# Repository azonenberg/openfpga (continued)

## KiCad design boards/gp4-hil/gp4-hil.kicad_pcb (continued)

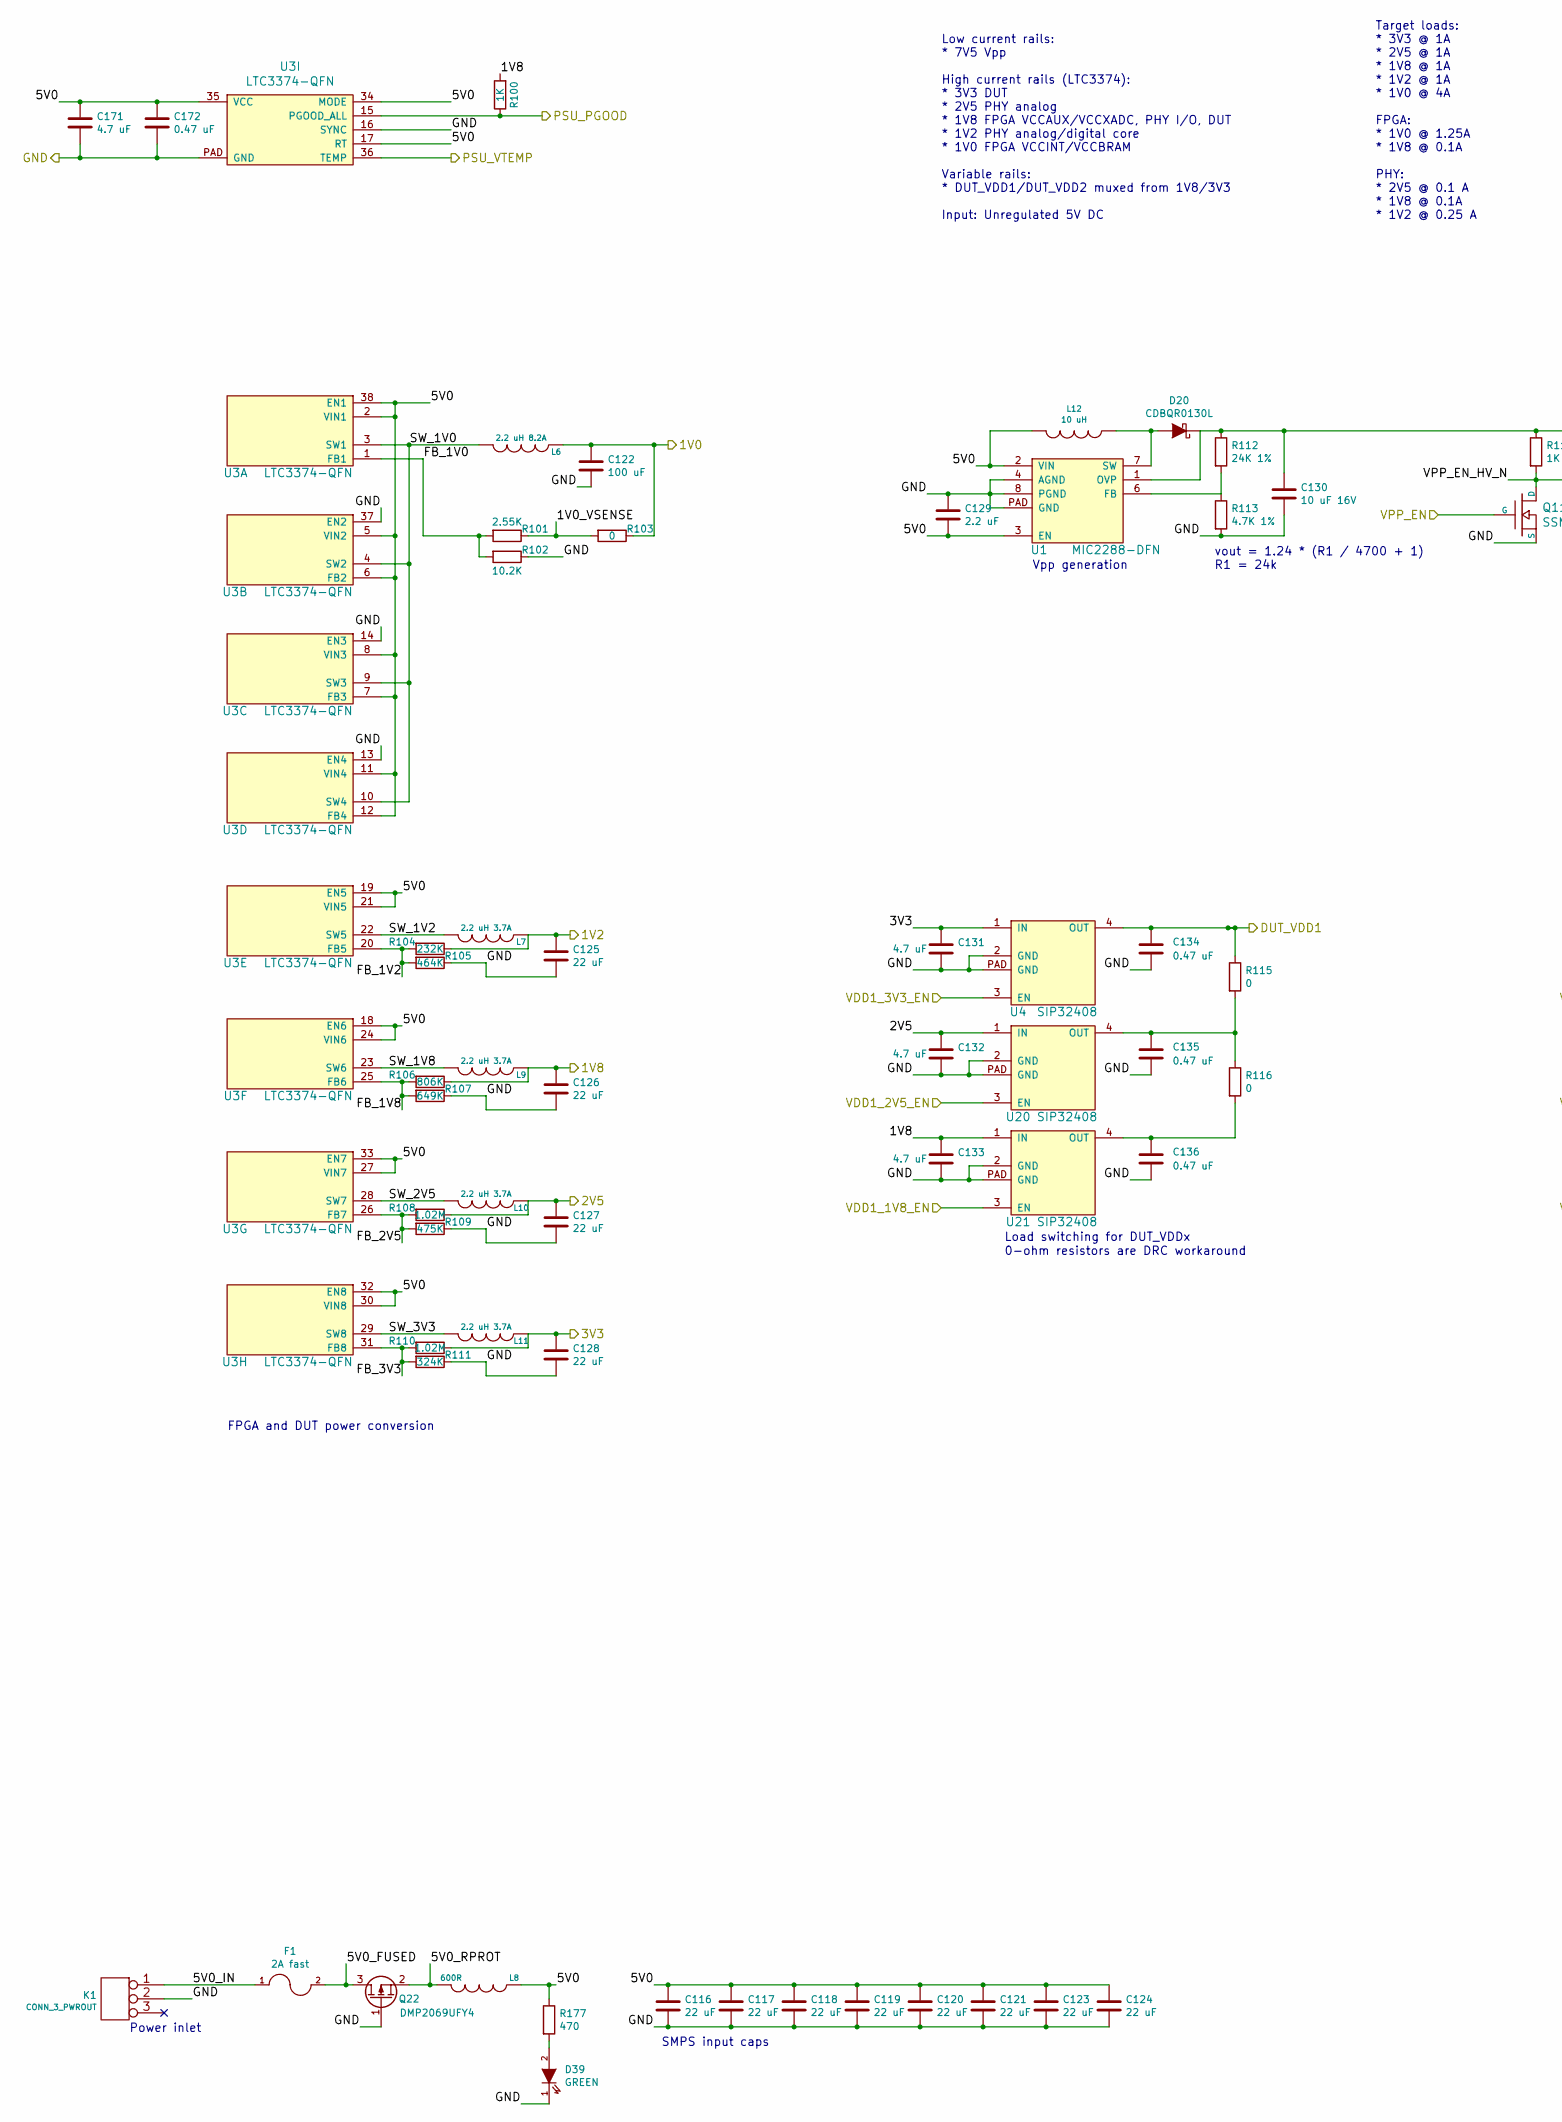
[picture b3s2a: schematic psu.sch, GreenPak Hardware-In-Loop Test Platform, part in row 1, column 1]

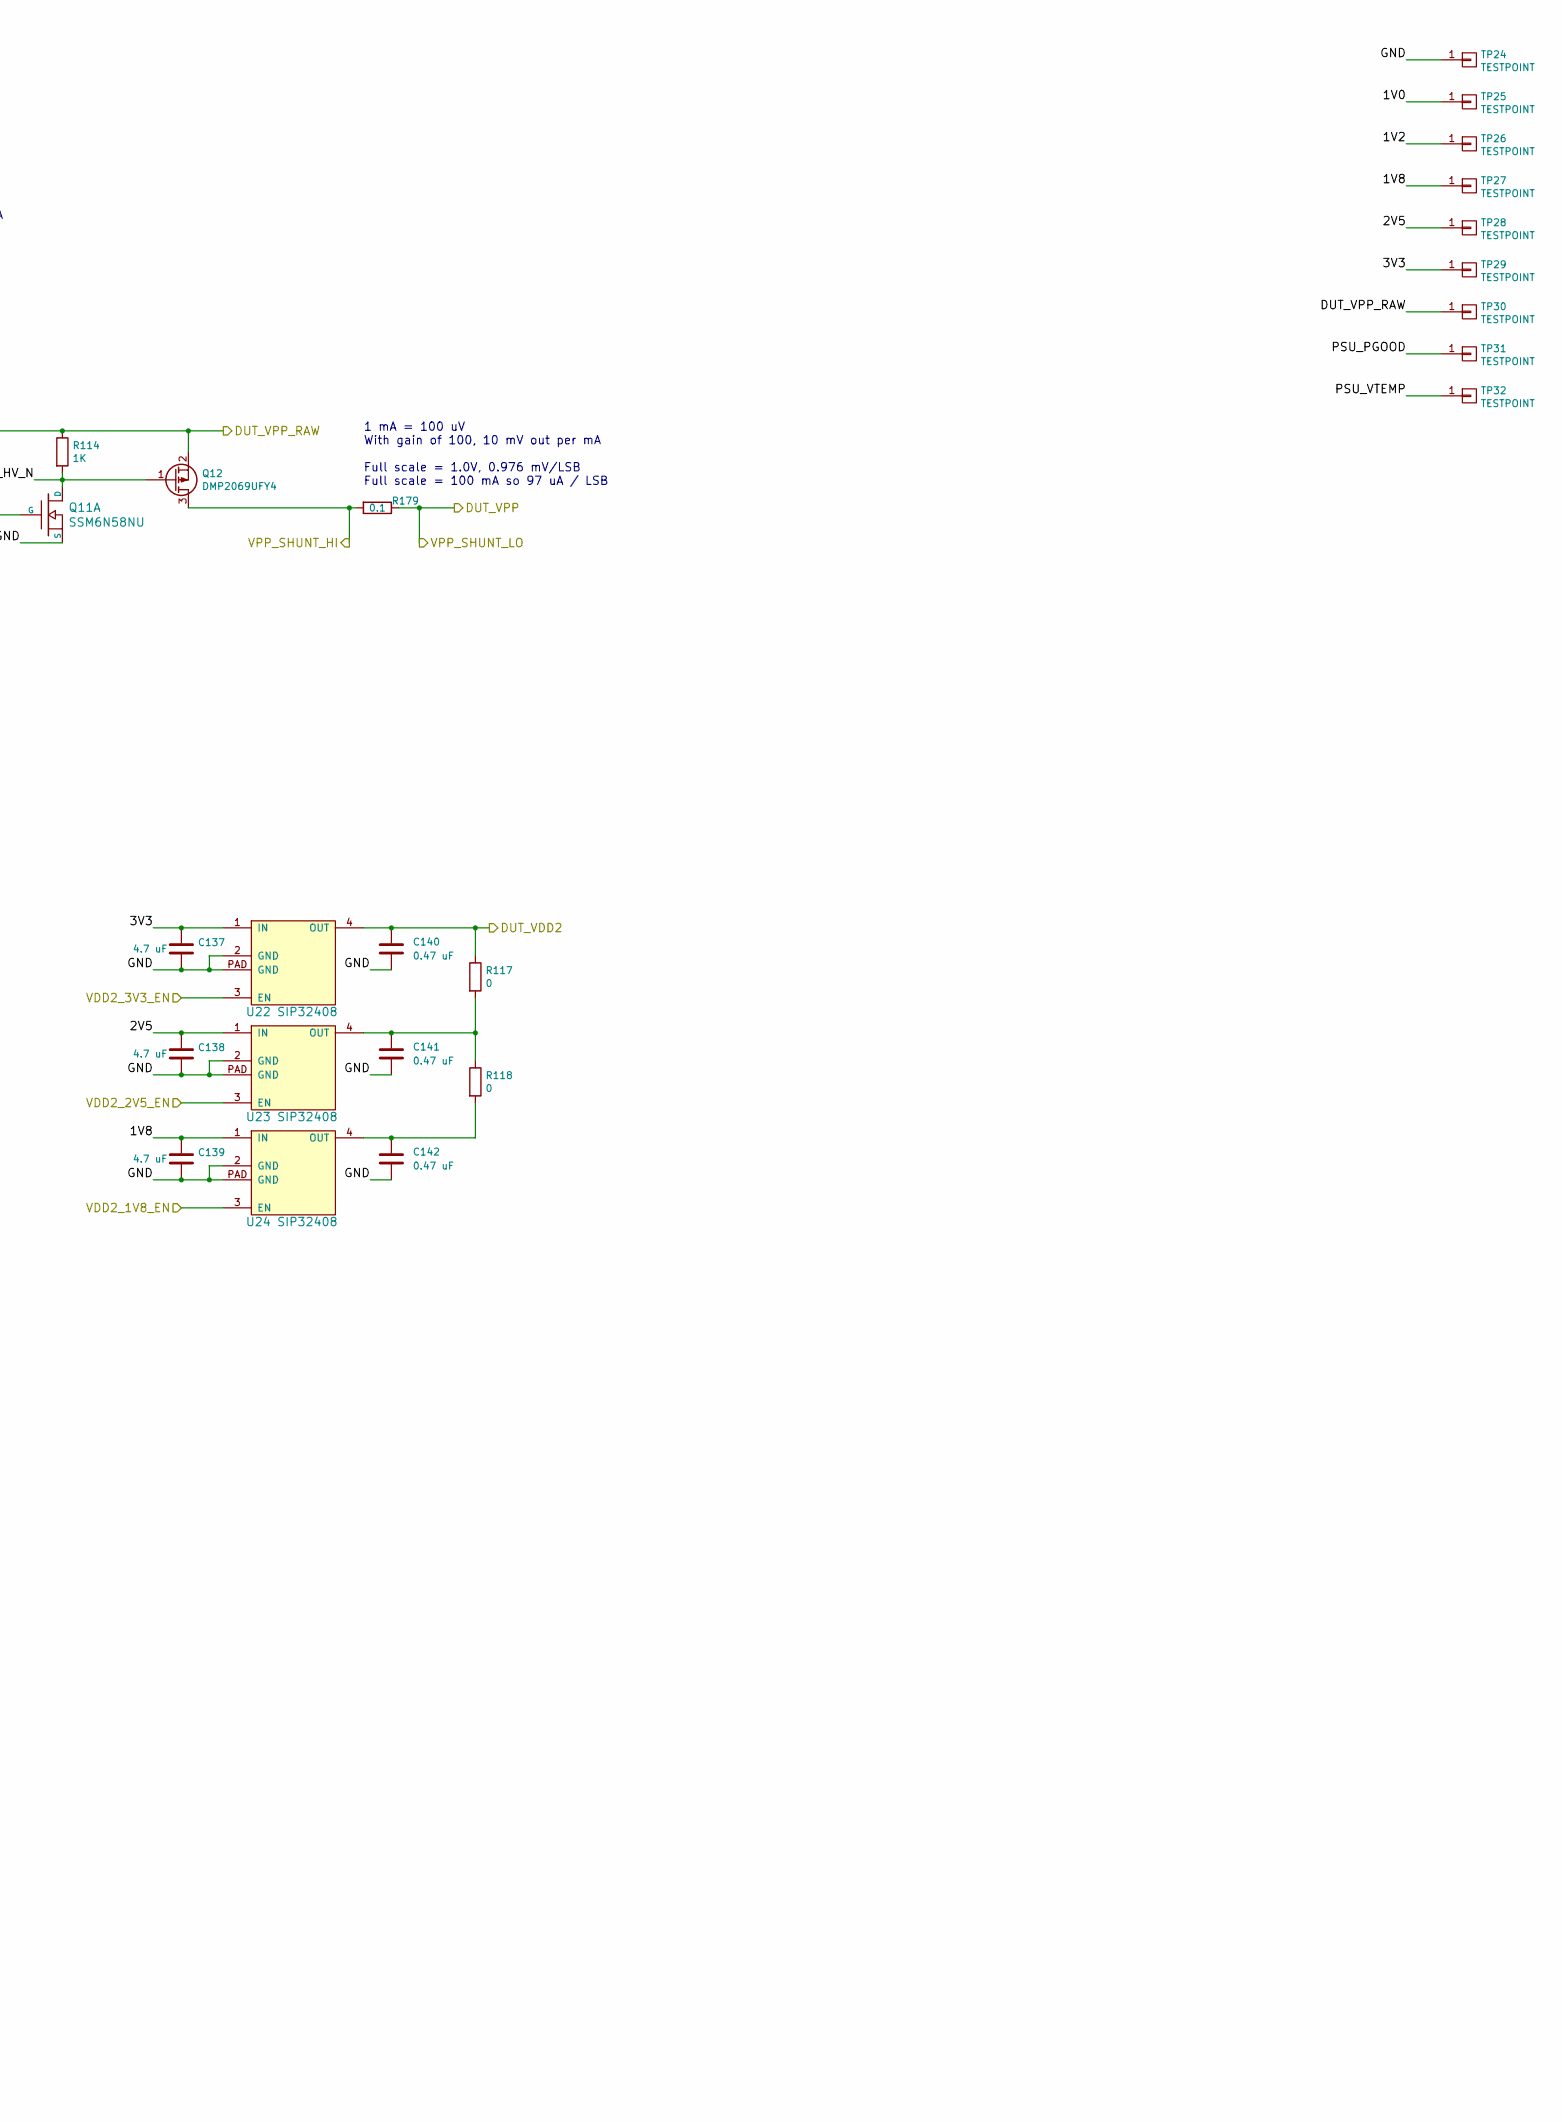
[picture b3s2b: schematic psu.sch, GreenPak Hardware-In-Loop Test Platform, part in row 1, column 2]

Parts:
C116, C117, C118, C119, C120, C121, C123, C124, C125, C126, C127, C128: 22 uF; EIA_1206_CAP_NOSILK
C122: 100 uF; EIA_1210_CAP_NOSILK
C129: 2.2 uF; EIA_1206_CAP_NOSILK
C130: 10 uF 16V; EIA_1206_CAP_NOSILK
C131, C132, C133, C137, C138, C139, C171: 4.7 uF; EIA_0603_CAP_NOSILK
C134, C135, C136, C140, C141, C142, C172: 0.47 uF; EIA_0402_CAP_NOSILK
D20: CDBQR0130L; EIA_0402_LED
D39: GREEN; EIA_0603_LED
F1: 2A fast; EIA_0402_RES_NOSILK
K1: CONN_3_PWROUT; CONN_CUI_PJ-058BH_HIPWR_BARREL_NOSLOT
L6: 2.2 uH 8.2A; INDUCTOR_TDK_SPM6530
L7, L9, L10, L11: 2.2 uH 3.7A; INDUCTOR_YUDEN_NR6028
L8: 600R; EIA_0603_INDUCTOR_NOSILK
L12: 10 uH; EIA_1210_CAP_NOSILK
Q11: SSM6N58NU; DFN_6_0.65MM_2x2MM_GDS
Q12, Q22: DMP2069UFY4; DFN_3_DIODES_X2DFN2015-3
R100, R114: 1K; EIA_0402_RES_NOSILK
R101: 2.55K; EIA_0402_RES_NOSILK
R102: 10.2K; EIA_0402_RES_NOSILK
R103, R115, R116, R117, R118: 0; EIA_0402_RES_NOSILK
R104: 232K; EIA_0402_RES_NOSILK
R105: 464K; EIA_0402_RES_NOSILK
R106: 806K; EIA_0402_RES_NOSILK
R107: 649K; EIA_0402_RES_NOSILK
R108, R110: 1.02M; EIA_0402_RES_NOSILK
R109: 475K; EIA_0402_RES_NOSILK
R111: 324K; EIA_0402_RES_NOSILK
R112: 24K 1%; EIA_0402_RES_NOSILK
R113: 4.7K 1%; EIA_0402_RES_NOSILK
R177: 470; EIA_0402_RES_NOSILK
R179: 0.1; EIA_0402_RES_NOSILK
TP24, TP25, TP26, TP27, TP28, TP29, TP30, TP31, TP32: TESTPOINT; TESTPOINT_SMT_KEYSTONE_5016
U1: MIC2288-DFN; DFN_8_0.5MM_2x2MM
U3: LTC3374-QFN; QFN_38_0.5MM_5x7MM
U4, U20, U21, U22, U23, U24: SIP32408; DFN_4_0.5MM_1.6x1.2MM

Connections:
/Analog IO/1V8: C126.1, C133.1, C139.1, L9.1, R100.2, R106.1, TP27.1, U21.1 (IN), U24.1 (IN); also elsewhere on the board
/Analog IO/2V5: C127.1, C132.1, C138.1, L10.1, R108.1, TP28.1, U20.1 (IN), U23.1 (IN); also elsewhere on the board
/Analog IO/3V3: C128.1, C131.1, C137.1, L11.1, R110.1, TP29.1, U4.1 (IN), U22.1 (IN); also elsewhere on the board
/Analog IO/DUT_GPIO2: R179.1; also elsewhere on the board
/Analog IO/DUT_VDD1: C134.1, R115.1, U4.4 (OUT); also elsewhere on the board
/Analog IO/DUT_VDD2: C140.1, R117.1, U22.4 (OUT); also elsewhere on the board
/Analog IO/DUT_VPP: C130.1, D20.1 (K), Q12.2 (S), R112.1, R114.1, TP30.1, U1.1 (OVP); also elsewhere on the board
/Analog IO/GND: C116.2, C117.2, C118.2, C119.2, C120.2, C121.2, C122.2, C123.2, C124.2, C125.2, C126.2, C127.2, C128.2, C129.1, C130.2, C131.2, C132.2, C133.2, C134.2, C135.2, C136.2, C137.2, C138.2, C139.2, C140.2, C141.2, C142.2, C171.2, C172.2, D39.1 (K), K1.2 (PM), Q11.S1 (S), Q22.1 (G), R102.1, R105.1, R107.1, R109.1, R111.1, R113.2, TP24.1, U1.4 (AGND), U1.8 (PGND), U1.PAD (GND), U3.13 (EN4), U3.14 (EN3), U3.16 (SYNC), U3.37 (EN2), U3.PAD (GND), U4.2 (GND), U4.PAD (GND), U20.2 (GND), U20.PAD (GND), U21.2 (GND), U21.PAD (GND), U22.2 (GND), U22.PAD (GND), U23.2 (GND), U23.PAD (GND), U24.2 (GND), U24.PAD (GND); also elsewhere on the board
/Analog IO/PSU_VTEMP: TP32.1, U3.36 (TEMP); also elsewhere on the board
/Analog IO/VPP_SHUNT_HI: Q12.3 (D), R179.2; also elsewhere on the board
/Ethernet + JTAG/1V2: C125.1, L7.1, R104.1, TP26.1; also elsewhere on the board
/Ethernet + JTAG/VDD1_1V8_EN: U21.3 (EN); also elsewhere on the board
/Ethernet + JTAG/VDD1_2V5_EN: U20.3 (EN); also elsewhere on the board
/Ethernet + JTAG/VDD1_3V3_EN: U4.3 (EN); also elsewhere on the board
/Ethernet + JTAG/VDD2_1V8_EN: U24.3 (EN); also elsewhere on the board
/Ethernet + JTAG/VDD2_2V5_EN: U23.3 (EN); also elsewhere on the board
/Ethernet + JTAG/VDD2_3V3_EN: U22.3 (EN); also elsewhere on the board
/Ethernet + JTAG/VPP_EN: Q11.G1 (G); also elsewhere on the board
/FPGA support/1V0: C122.1, L6.1, R103.1, TP25.1; also elsewhere on the board
/FPGA support/PSU_PGOOD: R100.1, TP31.1, U3.15 (PGOOD_ALL); also elsewhere on the board
/Power supply/1V0_VSENSE: R101.1, R103.2
/Power supply/5V0: C116.1, C117.1, C118.1, C119.1, C120.1, C121.1, C123.1, C124.1, C129.2, C171.1, C172.1, L8.1, L12.2, R177.1, U1.2 (VIN), U1.3 (EN), U3.2 (VIN1), U3.5 (VIN2), U3.6 (FB2), U3.7 (FB3), U3.8 (VIN3), U3.11 (VIN4), U3.12 (FB4), U3.17 (RT), U3.18 (EN6), U3.19 (EN5), U3.21 (VIN5), U3.24 (VIN6), U3.27 (VIN7), U3.30 (VIN8), U3.32 (EN8), U3.33 (EN7), U3.34 (MODE), U3.35 (VCC), U3.38 (EN1)
/Power supply/5V0_FUSED: F1.2, Q22.3 (D)
/Power supply/5V0_IN: F1.1, K1.1
/Power supply/5V0_RPROT: L8.2, Q22.2 (S)
/Power supply/FB_1V0: R101.2, R102.2, U3.1 (FB1)
/Power supply/FB_1V2: R104.2, R105.2, U3.20 (FB5)
/Power supply/FB_1V8: R106.2, R107.2, U3.25 (FB6)
/Power supply/FB_2V5: R108.2, R109.2, U3.26 (FB7)
/Power supply/FB_3V3: R110.2, R111.2, U3.31 (FB8)
/Power supply/SW_1V0: L6.2, U3.3 (SW1), U3.4 (SW2), U3.9 (SW3), U3.10 (SW4)
/Power supply/SW_1V2: L7.2, U3.22 (SW5)
/Power supply/SW_1V8: L9.2, U3.23 (SW6)
/Power supply/SW_2V5: L10.2, U3.28 (SW7)
/Power supply/SW_3V3: L11.2, U3.29 (SW8)
/Power supply/VPP_EN_HV_N: Q11.D1 (D), Q12.1 (G), R114.2
unnamed: C135.1, R115.2, R116.1, U20.4 (OUT)
unnamed: C136.1, R116.2, U21.4 (OUT)
unnamed: C141.1, R117.2, R118.1, U23.4 (OUT)
unnamed: C142.1, R118.2, U24.4 (OUT)
unnamed: D20.2 (A), L12.1, U1.7 (SW)
unnamed: D39.2 (A), R177.2
unnamed: R112.2, R113.1, U1.6 (FB)

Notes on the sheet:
Low current rails: * 7V5 Vpp High current rails (LTC3374): * 3V3 DUT * 2V5 PHY analog * 1V8 FPGA VCCAUX/VCCXADC, PHY I/O, DUT * 1V2 PHY analog/digital core * 1V0 FPGA VCCINT/VCCBRAM Variable rails: * DUT_VDD1/DUT_VDD2 muxed from 1V8/3V3 Input: Unregulated 5V DC
Power inlet
Target loads: * 3V3 @ 1A * 2V5 @ 1A * 1V8 @ 1A * 1V2 @ 1A * 1V0 @ 4A FPGA: * 1V0 @ 1.25A * 1V8 @ 0.1A PHY: * 2V5 @ 0.1 A * 1V8 @ 0.1A * 1V2 @ 0.25 A
SMPS input caps
vout = 1.24 * (R1 / 4700 + 1) R1 = 24k
Load switching for DUT_VDDx
Vpp generation
FPGA and DUT power conversion
0-ohm resistors are DRC workaround
1 mA = 100 uV With gain of 100, 10 mV out per mA Full scale = 1.0V, 0.976 mV/LSB Full scale = 100 mA so 97 uA / LSB

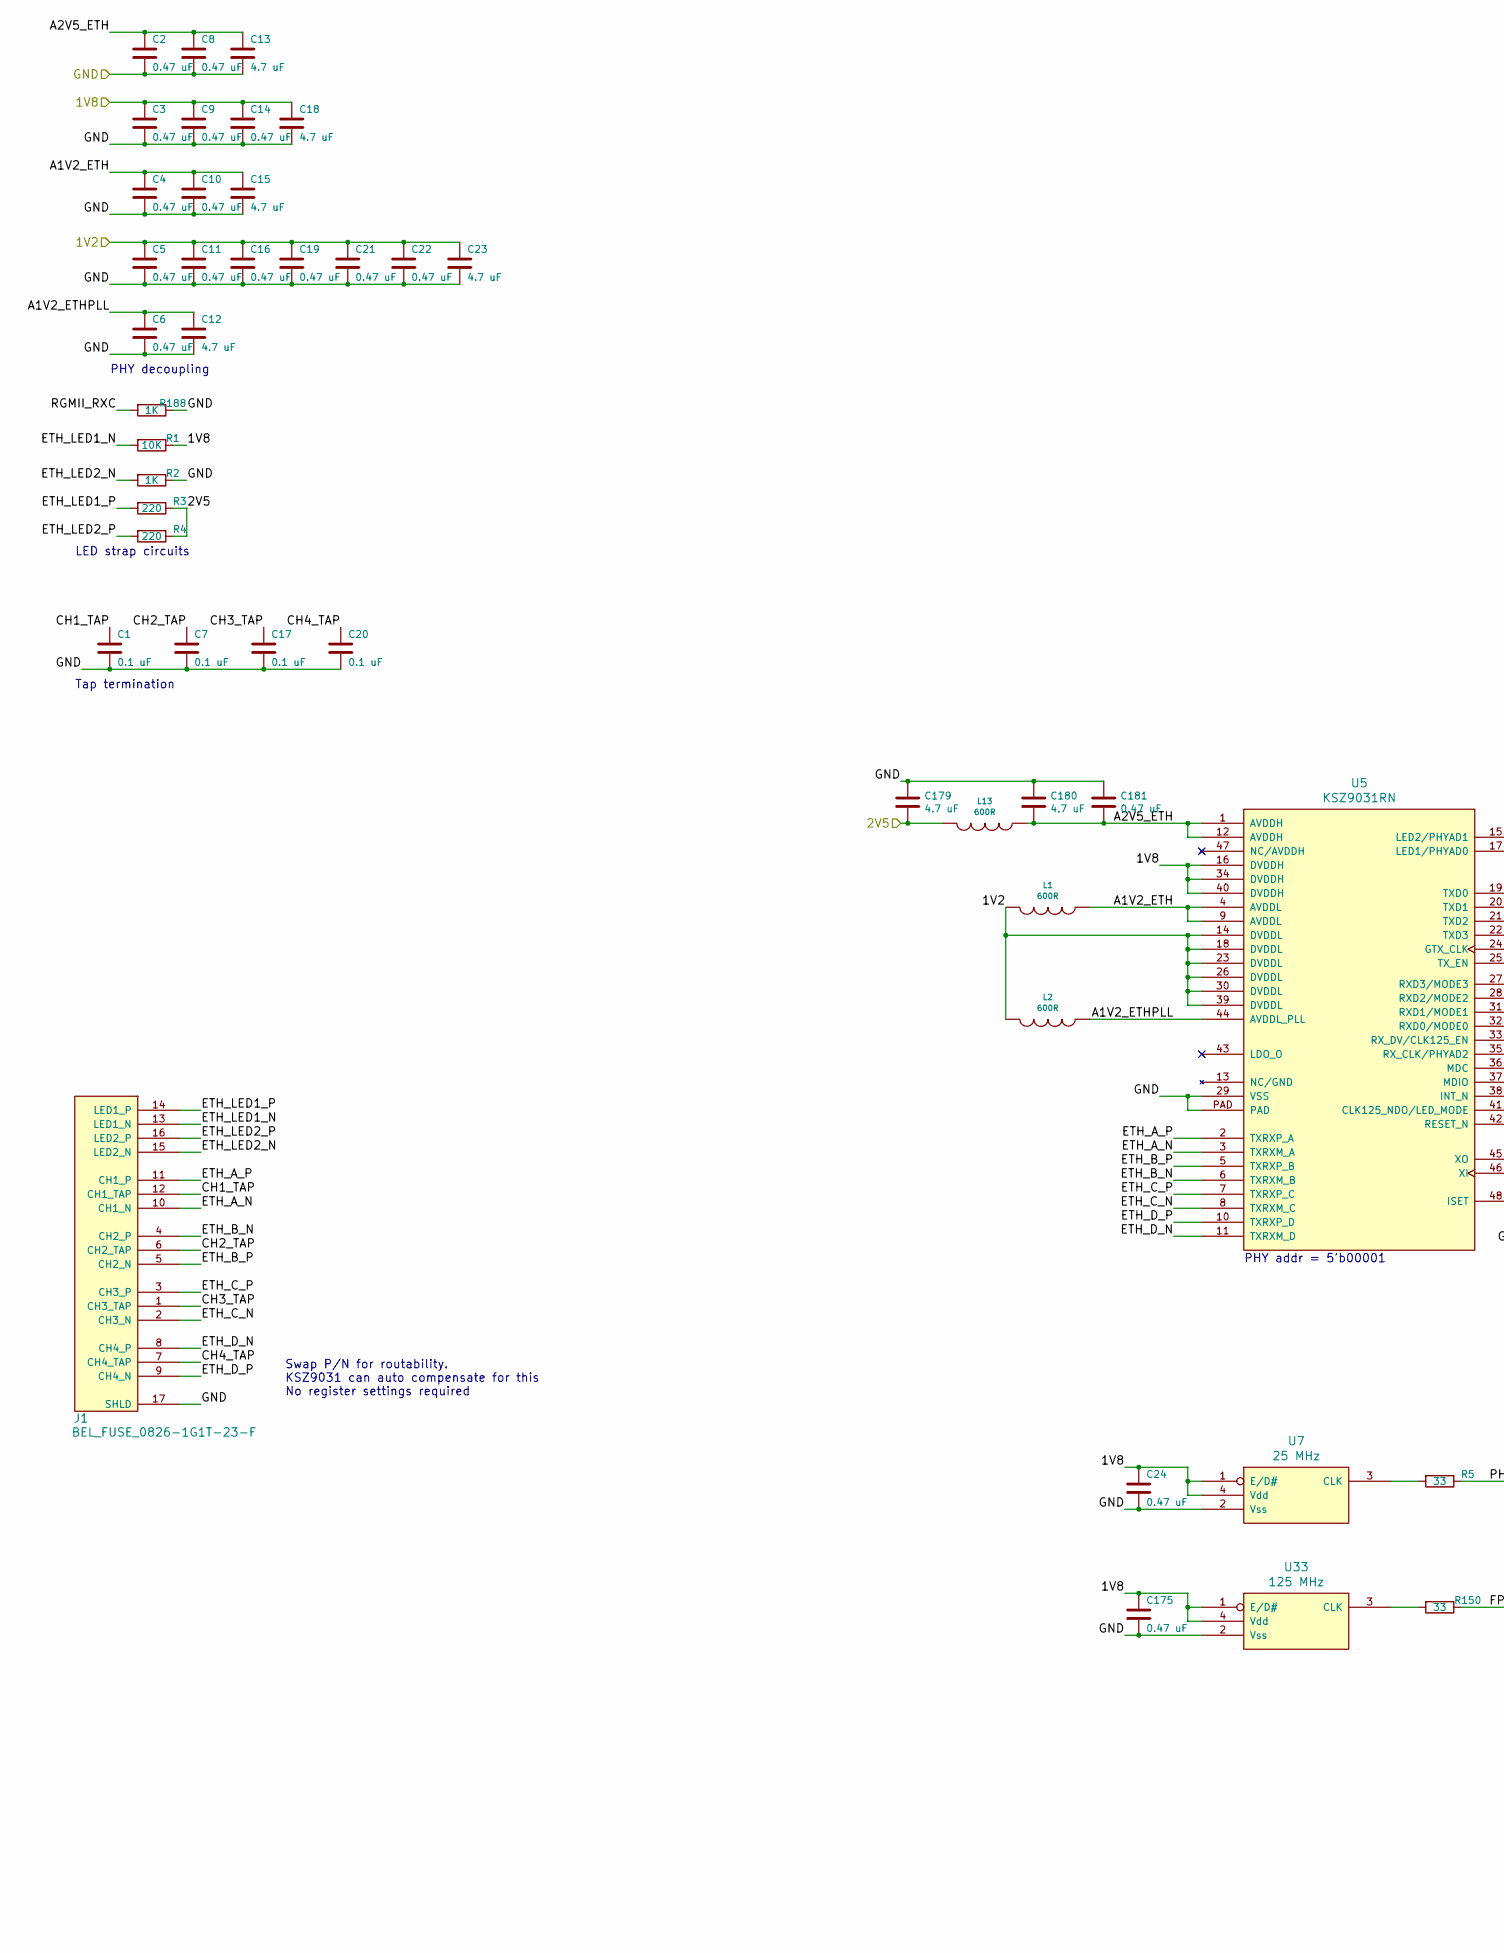
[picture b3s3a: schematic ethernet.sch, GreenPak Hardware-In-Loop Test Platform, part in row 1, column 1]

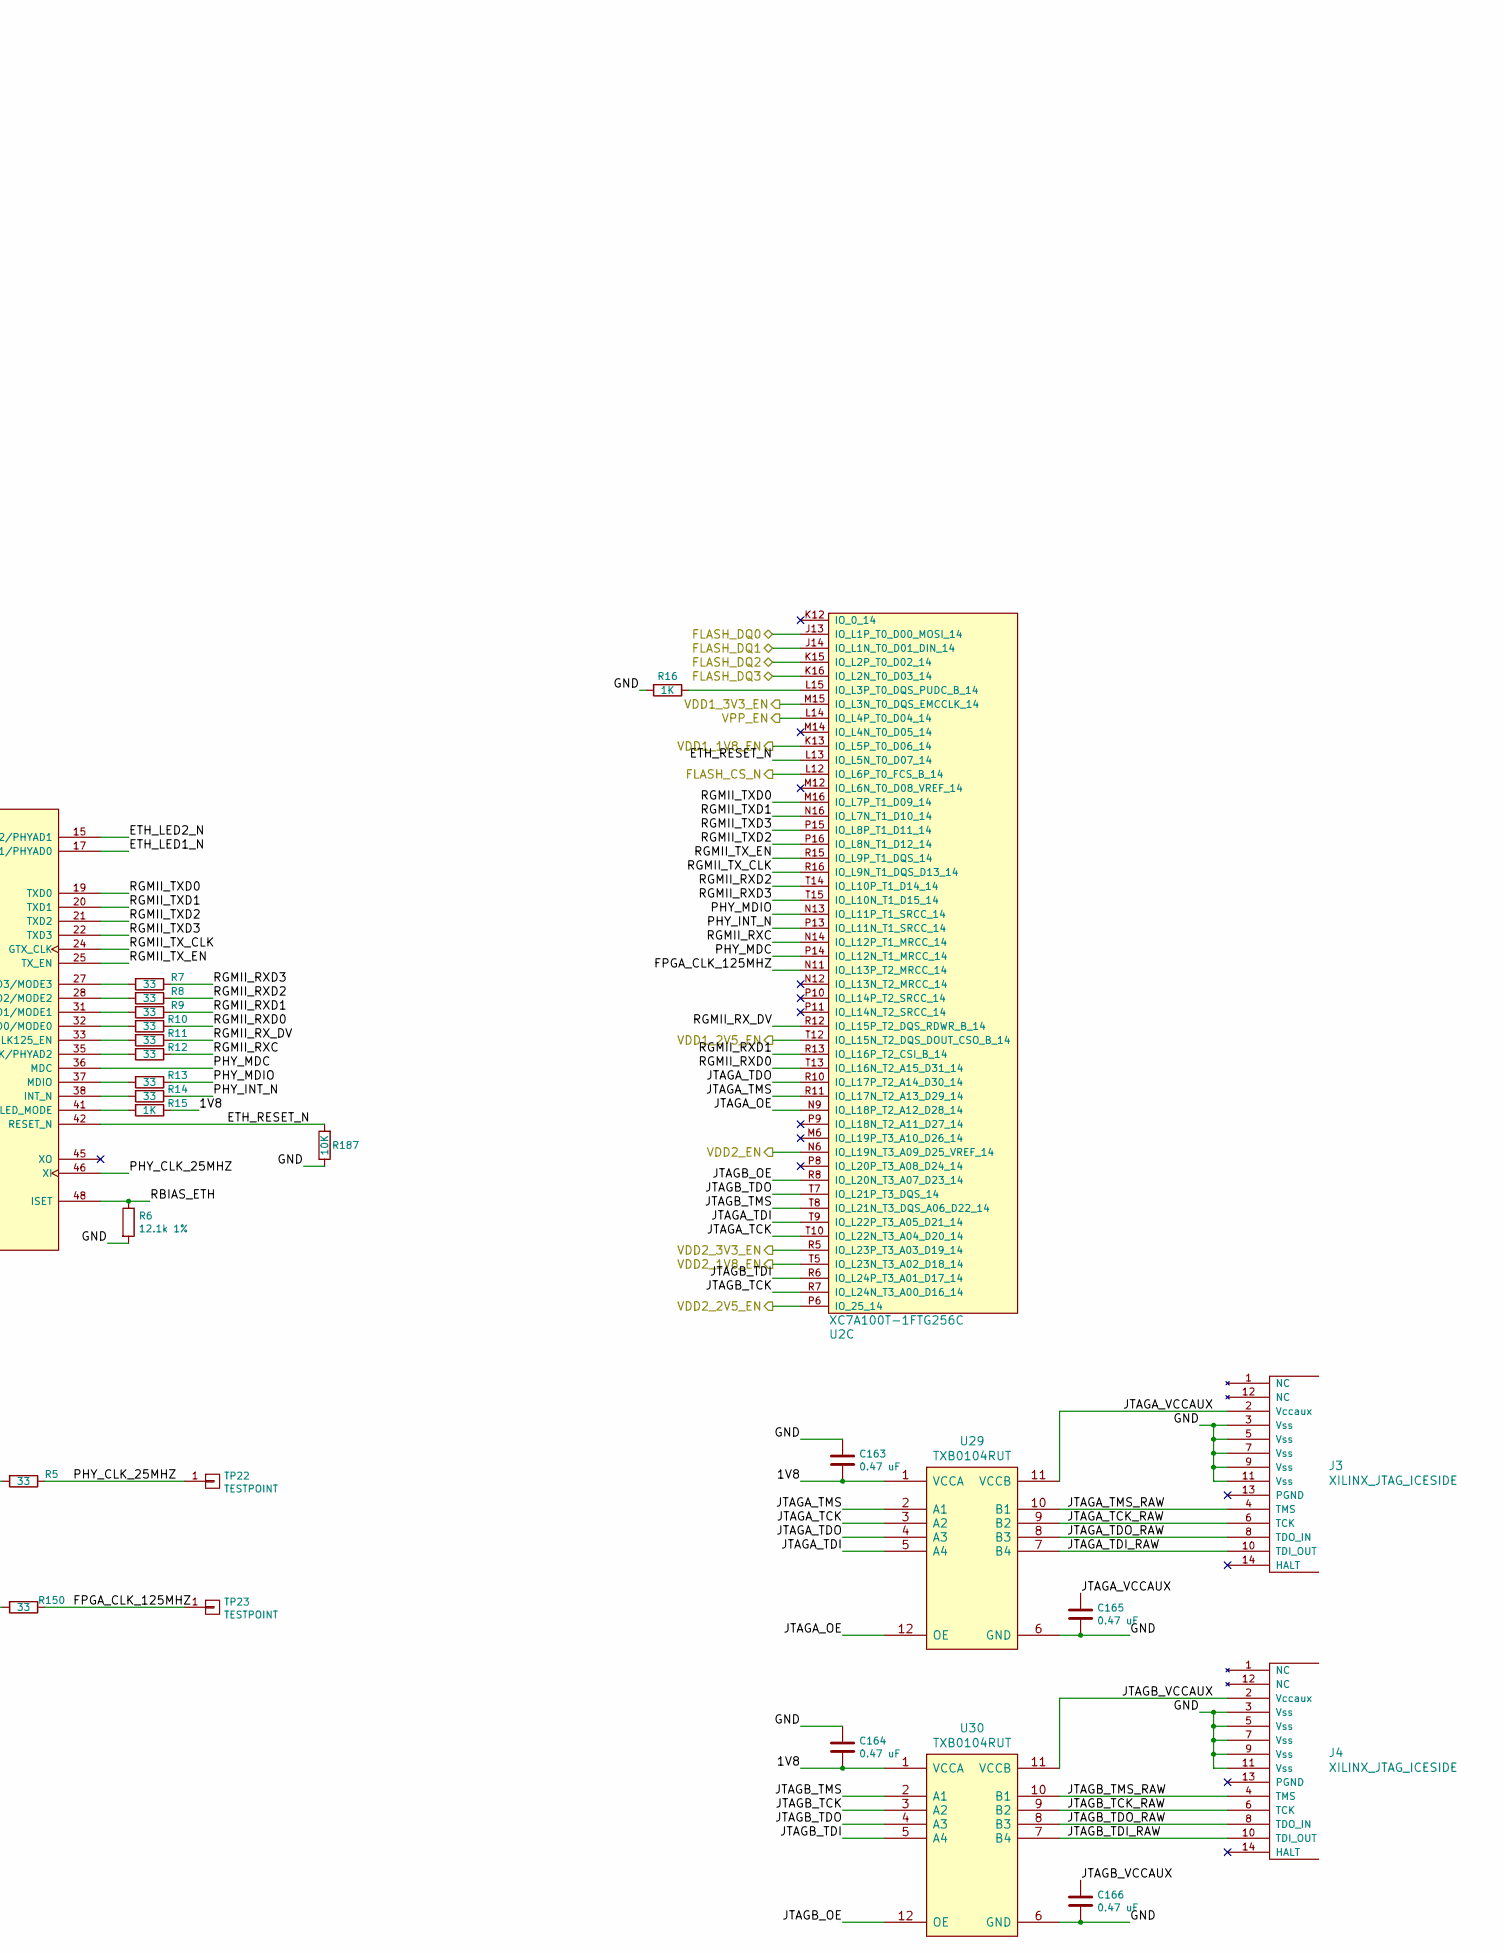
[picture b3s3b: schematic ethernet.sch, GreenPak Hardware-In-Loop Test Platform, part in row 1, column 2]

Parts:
C1, C7, C17, C20: 0.1 uF; EIA_0402_CAP_NOSILK
C2, C3, C4, C5, C6, C8, C9, C10, C11, C14, C16, C19, C21, C22, C24, C163, C164, C165, C166, C175, C181: 0.47 uF; EIA_0402_CAP_NOSILK
C12, C13, C15, C18, C23, C179, C180: 4.7 uF; EIA_0603_CAP_NOSILK
J1: BEL_FUSE_0826-1G1T-23-F; CONN_BELFUSE_0826_1G1T_23_F
J3, J4: XILINX_JTAG_ICESIDE; XILINX_JTAG_PTH_MOLEX_0878311420
L1, L2, L13: 600R; EIA_0603_INDUCTOR_NOSILK
R1, R187: 10K; EIA_0402_RES_NOSILK
R2, R15, R16, R188: 1K; EIA_0402_RES_NOSILK
R3, R4: 220; EIA_0402_RES_NOSILK
R5, R7, R8, R9, R10, R11, R12, R13, R14, R150: 33; EIA_0402_RES_NOSILK
R6: 12.1k 1%; EIA_0402_RES_NOSILK
TP22, TP23: TESTPOINT; TESTPOINT_SMT_0.5MM
U2: XC7A100T-1FTG256C; BGA_256_17x17_FULLARRAY_1MM
U5: KSZ9031RN; QFN_48_0.5MM_7x7MM
U7: 25 MHz; OSCILLATOR_2.0x1.6
U29, U30: TXB0104RUT; QFN_12_0.4MM_2x2MM
U33: 125 MHz; OSCILLATOR_2.0x1.6

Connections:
/Analog IO/1V8: C3.1, C9.1, C14.1, C18.1, C24.1, C163.2, C164.2, C175.1, R1.1, R15.1, U5.16 (DVDDH), U5.34 (DVDDH), U5.40 (DVDDH), U7.1 (E/D#), U7.4 (Vdd), U29.1 (VCCA), U30.1 (VCCA), U33.1 (E/D#), U33.4 (Vdd); also elsewhere on the board
/Analog IO/2V5: C179.2, L13.2, R3.1, R4.1; also elsewhere on the board
/Analog IO/GND: C1.2, C2.2, C3.2, C4.2, C5.2, C6.2, C7.2, C8.2, C9.2, C10.2, C11.2, C12.2, C13.2, C14.2, C15.2, C16.2, C17.2, C18.2, C19.2, C20.2, C21.2, C22.2, C23.2, C24.2, C163.1, C164.1, C165.2, C166.2, C175.2, C179.1, C180.1, C181.1, J1.17 (SHLD), J3.3 (Vss), J3.5 (Vss), J3.7 (Vss), J3.9 (Vss), J3.11 (Vss), J4.3 (Vss), J4.5 (Vss), J4.7 (Vss), J4.9 (Vss), J4.11 (Vss), R2.1, R6.2, R16.2, R187.1, R188.1, U5.29 (VSS), U5.PAD, U7.2 (Vss), U29.6 (GND), U30.6 (GND), U33.2 (Vss); also elsewhere on the board
/DUT/DUT_VDD2_EN: U2.N6 (IO_L19N_T3_A09_D25_VREF_14); also elsewhere on the board
/Ethernet + JTAG/1V2: C5.1, C11.1, C16.1, C19.1, C21.1, C22.1, C23.1, L1.2, L2.2, U5.14 (DVDDL), U5.18 (DVDDL), U5.23 (DVDDL), U5.26 (DVDDL), U5.30 (DVDDL), U5.39 (DVDDL); also elsewhere on the board
/Ethernet + JTAG/A1V2_ETH: C4.1, C10.1, C15.1, L1.1, U5.4 (AVDDL), U5.9 (AVDDL)
/Ethernet + JTAG/A1V2_ETHPLL: C6.1, C12.1, L2.1, U5.44 (AVDDL_PLL)
/Ethernet + JTAG/A2V5_ETH: C2.1, C8.1, C13.1, C180.2, C181.2, L13.1, U5.1 (AVDDH), U5.12 (AVDDH)
/Ethernet + JTAG/CH1_TAP: C1.1, J1.12 (CH1_TAP)
/Ethernet + JTAG/CH2_TAP: C7.1, J1.6 (CH2_TAP)
/Ethernet + JTAG/CH3_TAP: C17.1, J1.1 (CH3_TAP)
/Ethernet + JTAG/CH4_TAP: C20.1, J1.7 (CH4_TAP)
/Ethernet + JTAG/ETH_A_N: J1.10 (CH1_N), U5.3 (TXRXM_A)
/Ethernet + JTAG/ETH_A_P: J1.11 (CH1_P), U5.2 (TXRXP_A)
/Ethernet + JTAG/ETH_B_N: J1.4 (CH2_P), U5.6 (TXRXM_B)
/Ethernet + JTAG/ETH_B_P: J1.5 (CH2_N), U5.5 (TXRXP_B)
/Ethernet + JTAG/ETH_C_N: J1.2 (CH3_N), U5.8 (TXRXM_C)
/Ethernet + JTAG/ETH_C_P: J1.3 (CH3_P), U5.7 (TXRXP_C)
/Ethernet + JTAG/ETH_D_N: J1.8 (CH4_P), U5.11 (TXRXM_D)
/Ethernet + JTAG/ETH_D_P: J1.9 (CH4_N), U5.10 (TXRXP_D)
/Ethernet + JTAG/ETH_LED1_N: J1.13 (LED1_N), R1.2, U5.17 (LED1/PHYAD0)
/Ethernet + JTAG/ETH_LED1_P: J1.14 (LED1_P), R3.2
/Ethernet + JTAG/ETH_LED2_N: J1.15 (LED2_N), R2.2, U5.15 (LED2/PHYAD1)
/Ethernet + JTAG/ETH_LED2_P: J1.16 (LED2_P), R4.2
/Ethernet + JTAG/ETH_RESET_N: R187.2, U2.L13 (IO_L5N_T0_D07_14), U5.42 (RESET_N)
/Ethernet + JTAG/FLASH_CS_N: U2.L12 (IO_L6P_T0_FCS_B_14); also elsewhere on the board
/Ethernet + JTAG/FLASH_DQ0: U2.J13 (IO_L1P_T0_D00_MOSI_14); also elsewhere on the board
/Ethernet + JTAG/FLASH_DQ1: U2.J14 (IO_L1N_T0_D01_DIN_14); also elsewhere on the board
/Ethernet + JTAG/FLASH_DQ2: U2.K15 (IO_L2P_T0_D02_14); also elsewhere on the board
/Ethernet + JTAG/FLASH_DQ3: U2.K16 (IO_L2N_T0_D03_14); also elsewhere on the board
/Ethernet + JTAG/FPGA_CLK_125MHZ: R150.1, TP23.1, U2.N11 (IO_L13P_T2_MRCC_14)
/Ethernet + JTAG/JTAGA_OE: U2.N9 (IO_L18P_T2_A12_D28_14), U29.12 (OE)
/Ethernet + JTAG/JTAGA_TCK: U2.T10 (IO_L22N_T3_A04_D20_14), U29.3 (A2)
/Ethernet + JTAG/JTAGA_TCK_RAW: J3.6 (TCK), U29.9 (B2)
/Ethernet + JTAG/JTAGA_TDI: U2.T9 (IO_L22P_T3_A05_D21_14), U29.5 (A4)
/Ethernet + JTAG/JTAGA_TDI_RAW: J3.10 (TDI_OUT), U29.7 (B4)
/Ethernet + JTAG/JTAGA_TDO: U2.R10 (IO_L17P_T2_A14_D30_14), U29.4 (A3)
/Ethernet + JTAG/JTAGA_TDO_RAW: J3.8 (TDO_IN), U29.8 (B3)
/Ethernet + JTAG/JTAGA_TMS: U2.R11 (IO_L17N_T2_A13_D29_14), U29.2 (A1)
/Ethernet + JTAG/JTAGA_TMS_RAW: J3.4 (TMS), U29.10 (B1)
/Ethernet + JTAG/JTAGA_VCCAUX: C165.1, J3.2 (Vccaux), U29.11 (VCCB)
/Ethernet + JTAG/JTAGB_OE: U2.R8 (IO_L20N_T3_A07_D23_14), U30.12 (OE)
/Ethernet + JTAG/JTAGB_TCK: U2.R7 (IO_L24N_T3_A00_D16_14), U30.3 (A2)
/Ethernet + JTAG/JTAGB_TCK_RAW: J4.6 (TCK), U30.9 (B2)
/Ethernet + JTAG/JTAGB_TDI: U2.R6 (IO_L24P_T3_A01_D17_14), U30.5 (A4)
/Ethernet + JTAG/JTAGB_TDI_RAW: J4.10 (TDI_OUT), U30.7 (B4)
/Ethernet + JTAG/JTAGB_TDO: U2.T7 (IO_L21P_T3_DQS_14), U30.4 (A3)
/Ethernet + JTAG/JTAGB_TDO_RAW: J4.8 (TDO_IN), U30.8 (B3)
/Ethernet + JTAG/JTAGB_TMS: U2.T8 (IO_L21N_T3_DQS_A06_D22_14), U30.2 (A1)
/Ethernet + JTAG/JTAGB_TMS_RAW: J4.4 (TMS), U30.10 (B1)
/Ethernet + JTAG/JTAGB_VCCAUX: C166.1, J4.2 (Vccaux), U30.11 (VCCB)
/Ethernet + JTAG/PHY_CLK_25MHZ: R5.1, TP22.1, U5.46 (XI)
/Ethernet + JTAG/PHY_INT_N: R14.1, U2.P13 (IO_L11N_T1_SRCC_14)
/Ethernet + JTAG/PHY_MDC: U2.P14 (IO_L12N_T1_MRCC_14), U5.36 (MDC)
/Ethernet + JTAG/PHY_MDIO: R13.1, U2.N13 (IO_L11P_T1_SRCC_14)
/Ethernet + JTAG/RBIAS_ETH: R6.1, U5.48 (ISET)
/Ethernet + JTAG/RGMII_RXC: R12.1, R188.2, U2.N14 (IO_L12P_T1_MRCC_14)
/Ethernet + JTAG/RGMII_RXD0: R10.1, U2.T13 (IO_L16N_T2_A15_D31_14)
/Ethernet + JTAG/RGMII_RXD1: R9.1, U2.R13 (IO_L16P_T2_CSI_B_14)
/Ethernet + JTAG/RGMII_RXD2: R8.1, U2.T14 (IO_L10P_T1_D14_14)
/Ethernet + JTAG/RGMII_RXD3: R7.1, U2.T15 (IO_L10N_T1_D15_14)
/Ethernet + JTAG/RGMII_RX_DV: R11.1, U2.R12 (IO_L15P_T2_DQS_RDWR_B_14)
/Ethernet + JTAG/RGMII_TXD0: U2.M16 (IO_L7P_T1_D09_14), U5.19 (TXD0)
/Ethernet + JTAG/RGMII_TXD1: U2.N16 (IO_L7N_T1_D10_14), U5.20 (TXD1)
/Ethernet + JTAG/RGMII_TXD2: U2.P16 (IO_L8N_T1_D12_14), U5.21 (TXD2)
/Ethernet + JTAG/RGMII_TXD3: U2.P15 (IO_L8P_T1_D11_14), U5.22 (TXD3)
/Ethernet + JTAG/RGMII_TX_CLK: U2.R16 (IO_L9N_T1_DQS_D13_14), U5.24 (GTX_CLK)
/Ethernet + JTAG/RGMII_TX_EN: U2.R15 (IO_L9P_T1_DQS_14), U5.25 (TX_EN)
/Ethernet + JTAG/VDD1_1V8_EN: U2.K13 (IO_L5P_T0_D06_14); also elsewhere on the board
/Ethernet + JTAG/VDD1_2V5_EN: U2.T12 (IO_L15N_T2_DQS_DOUT_CSO_B_14); also elsewhere on the board
/Ethernet + JTAG/VDD1_3V3_EN: U2.M15 (IO_L3N_T0_DQS_EMCCLK_14); also elsewhere on the board
/Ethernet + JTAG/VDD2_1V8_EN: U2.T5 (IO_L23N_T3_A02_D18_14); also elsewhere on the board
/Ethernet + JTAG/VDD2_2V5_EN: U2.P6 (IO_25_14); also elsewhere on the board
/Ethernet + JTAG/VDD2_3V3_EN: U2.R5 (IO_L23P_T3_A03_D19_14); also elsewhere on the board
/Ethernet + JTAG/VPP_EN: U2.L14 (IO_L4P_T0_D04_14); also elsewhere on the board
unnamed: R5.2, U7.3 (CLK)
unnamed: R7.2, U5.27 (RXD3/MODE3)
unnamed: R8.2, U5.28 (RXD2/MODE2)
unnamed: R9.2, U5.31 (RXD1/MODE1)
unnamed: R10.2, U5.32 (RXD0/MODE0)
unnamed: R11.2, U5.33 (RX_DV/CLK125_EN)
unnamed: R12.2, U5.35 (RX_CLK/PHYAD2)
unnamed: R13.2, U5.37 (MDIO)
unnamed: R14.2, U5.38 (INT_N)
unnamed: R15.2, U5.41 (CLK125_NDO/LED_MODE)
unnamed: R16.1, U2.L15 (IO_L3P_T0_DQS_PUDC_B_14)
unnamed: R150.2, U33.3 (CLK)

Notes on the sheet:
LED strap circuits
PHY decoupling
Tap termination
PHY addr = 5'b00001
Swap P/N for routability. KSZ9031 can auto compensate for this No register settings required
